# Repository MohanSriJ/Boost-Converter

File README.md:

<div align="center">
  <h1>⚡ DC-DC Boost Converter PCB</h1>
  <h3>🔋 Adjustable Boost Converter Designed in KiCad</h3>
  <p><strong>A custom PCB implementation of an XL6009-based DC-DC boost converter with adjustable output voltage, custom footprints, 3D models, and complete KiCad design files.</strong></p>
</div>

---

## 🎯 Project Overview

This project is a **custom DC-DC Boost Converter PCB** designed using **KiCad**.

The design is based on the **XL6009 boost converter** and includes power filtering, feedback-based output adjustment, custom component footprints, and 3D visualization.

The repository contains the complete design workflow:

`Schematic → PCB Layout → Custom Components → 3D Visualization`

---

## 💡 Project Highlights

### 🔑 Key Capabilities

1. **⚡ XL6009 Boost Converter**

   Implements the XL6009 as the main boost conversion element.

2. **🎚️ Adjustable Output Voltage**

   A potentiometer is used in the feedback network to adjust the converter output.

3. **🔌 Input & Output Filtering**

   Capacitors are used for input and output filtering to support stable converter operation.

4. **🧩 Custom KiCad Components**

   Custom footprints, schematic symbols, and 3D models are included for selected components.

5. **🖥️ Complete PCB Design**

   Includes schematic capture, component placement, routing, copper zones, vias, and PCB visualization.

6. **🧊 3D PCB Visualization**

   KiCad's 3D Viewer is used to verify component placement and visualize the assembled board.

---

## 🧰 Main Components

| Component | Description |
|---|---|
| **XL6009** | DC-DC Boost Converter |
| **DR125-3R3-R** | SMD Power Inductor |
| **SS34** | Schottky Diode |
| **47 µF / 50 V** | Input Capacitor |
| **1 µF** | Input/Output Capacitors |
| **220 µF / 50 V** | Output Capacitor |
| **1 kΩ** | Feedback Resistor |
| **50 kΩ** | Adjustable Potentiometer |
| **Connectors** | Input and Output Connections |

---

## 📐 Schematic Design

The schematic contains the complete boost converter circuit and its supporting components.

### Main Circuit Sections

- 🔌 Input power connection
- 🧲 Power inductor
- ⚡ XL6009 boost converter
- 🔋 Schottky diode
- 🧹 Input filtering
- 🧹 Output filtering
- 🎚️ Feedback voltage adjustment
- 🔌 Output connection

### Schematic

---

## 🖥️ PCB Design

The PCB was designed as a **2-layer board** using KiCad.

The layout focuses on practical component placement, power routing, grounding, and compact organization.

### PCB Design Includes

- 🧩 SMD and through-hole components
- ⚡ Wide power traces
- 🌐 Ground copper zone
- 🔗 Through vias
- 📍 Organized component placement
- 🔌 Input and output terminals
- 🧊 3D component models

### PCB Layout

---

## 🧩 Custom Components

### ⚡ XL6009

A custom KiCad component was created for the XL6009 module.

The folder contains:

- 📐 Custom schematic symbol
- 🧩 Custom PCB footprint
- 🧊 STEP 3D model
- 🖼️ 3D reference image
- 📖 Import instructions

👉 [View XL6009 Resources](./XL6009/)

---

### 🧲 DR125-3R3-R

A custom KiCad component was created for the DR125-3R3-R power inductor.

The folder contains:

- 📐 Schematic symbol
- 🧩 Custom PCB footprint
- 🧊 STEP 3D model
- 🖼️ 3D reference image
- 📖 Import instructions

👉 [View DR125-3R3-R Resources](./DR125-3R3-R/)

---

## 🧊 3D PCB Visualization

The KiCad **3D Viewer** was used to inspect the final PCB design and verify component placement.

### 3D View

### Additional 3D View

---

## 🎥 3D Visualization Video

A 3D visualization video of the PCB is included with the project.

👉 [🎥 View 3D PCB Video](./media/video/)

---

## 📂 Project Documentation

The project is organized into separate sections for easier navigation.

- 📐 [Schematic](./media/schematic/)
- 🖥️ [PCB Layout](./media/pcb-layout/)
- 🧊 [3D View](./media/3d-view/)
- 🎥 [3D Video](./media/video/)
- ⚡ [XL6009 Custom Component](./XL6009/)
- 🧲 [DR125-3R3-R Custom Component](./DR125-3R3-R/)

---

## 🗂️ Repository Structure

```text
DC-DC-Boost-Converter/
│
├── media/
│   ├── schematic/
│   │   └── schematic.png
│   │
│   ├── pcb-layout/
│   │   └── pcb_layout.png
│   │
│   ├── 3d-view/
│   │   ├── 3d_view_1.png
│   │   └── 3d_view_2.png
│   │
│   └── video/
│       └── pcb_3d_view.mp4
│
├── XL6009/
│   ├── README.md
│   ├── XL6009.kicad_sym
│   ├── DPAK170P1435X465-6N.kicad_mod
│   ├── XL6009.step
│   ├── XL6009 3D.png
│   └── how-to-import
│
├── DR125-3R3-R/
│   ├── README.md
│   ├── DR125-3R3-R.kicad_sym
│   ├── INDM1250X1250X600.kicad_mod
│   ├── DR125-3R3-R.step
│   ├── DR125 3D.png
│   └── how-to-import
│
├── Boost Converter.kicad_pcb
├── Boost Converter.kicad_sch
├── Boost Converter.kicad_pro
├── Boost Converter.kicad_prl
└── fp-info-cache
```
## 🛠️ Design Files

The repository contains the complete KiCad project files.

| File Type | Purpose |
|---|---|
| `.kicad_sch` | Schematic design |
| `.kicad_pcb` | PCB layout |
| `.kicad_pro` | KiCad project configuration |
| `.kicad_mod` | Custom PCB footprints |
| `.kicad_sym` | Custom schematic symbols |
| `.step` | 3D component models |

---

## 💻 Software & Tools

### 🖥️ PCB Design

- **KiCad 7.x**

### 📐 Design Tools

- Schematic Capture
- PCB Layout
- Custom Footprint Creation
- Custom Symbol Creation
- STEP 3D Model Integration
- KiCad 3D Viewer

---

## 🔄 Design Workflow

```text
Circuit Concept
      ↓
Schematic Design
      ↓
Component Selection
      ↓
Custom Footprint Creation
      ↓
PCB Component Placement
      ↓
Power & Signal Routing
      ↓
Ground Copper Zone
      ↓
Design Verification
      ↓
3D Model Integration
      ↓
3D PCB Visualization
      ↓
Final PCB Design
```
---

## 📊 PCB Design Overview

| Parameter | Details |
|---|---|
| **Converter Type** | DC-DC Boost Converter |
| **Main Controller** | XL6009 |
| **PCB Layers** | 2 Layer |
| **Design Software** | KiCad 7.x |
| **PCB Type** | Custom Designed PCB |
| **Output** | Adjustable |
| **3D Visualization** | KiCad 3D Viewer |
| **Custom Components** | XL6009, DR125-3R3-R |

---

## ✨ Key Features

- ⚡ XL6009-based boost converter
- 🎚️ Adjustable output voltage
- 🔋 Input and output filtering
- 🧲 Dedicated power inductor
- 🔌 Input and output connectors
- 🧩 Custom KiCad footprints
- 📐 Custom schematic symbols
- 🧊 Custom STEP 3D models
- 🌐 Ground copper zone
- ⚡ Wide power traces
- 🔗 Through vias
- 🖥️ Complete 3D PCB visualization

---

## 📈 Project Status

- ✅ Schematic designed
- ✅ PCB layout completed
- ✅ Component placement completed
- ✅ Power routing completed
- ✅ Ground copper zone added
- ✅ Custom footprints created
- ✅ Custom schematic symbols created
- ✅ 3D models integrated
- ✅ PCB 3D visualization completed
- ✅ Project files organized for GitHub

---

## 🌍 Project Purpose

This project demonstrates the complete process of developing a custom power electronics PCB using KiCad.

It can serve as a reference for learning:

- 🔧 PCB design
- ⚡ Power electronics layout
- 📐 KiCad schematic design
- 🧩 Custom footprint creation
- 🧊 3D model integration
- 🔗 PCB routing
- 📚 Hardware documentation

---

## 👨‍💻 Author

**MohanSriJ**

---

## 📜 License

This project is provided for **educational and design reference purposes**.

Feel free to explore the design files and documentation to understand the PCB development workflow.

---

<div align="center">

⚡ **Designed with KiCad** | 🔋 **Built for Power Electronics** | 🖥️ **Fully Documented**

</div>

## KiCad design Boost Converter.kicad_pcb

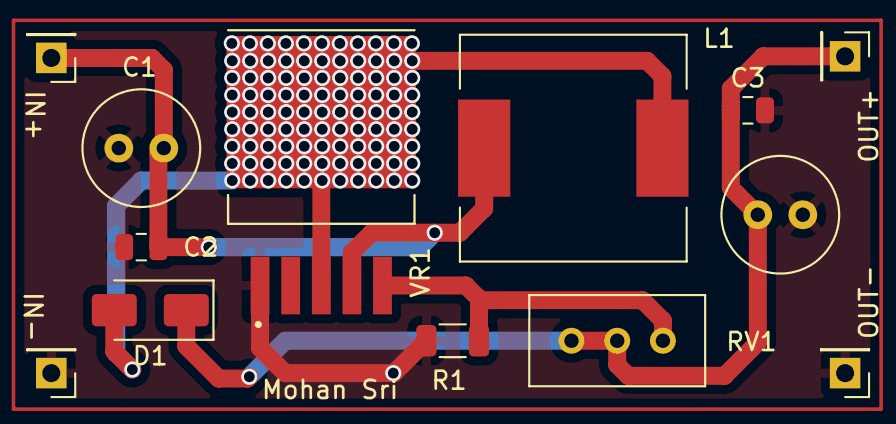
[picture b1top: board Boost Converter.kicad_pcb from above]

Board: 2 copper layers, 13 parts (0 on the bottom side), 5 nets.

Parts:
C1: 47uF/50V; C_Radial_D6.3mm_H11.0mm_P2.50mm
C2, C3: 1uF; C_0805_2012Metric
C4: 220uF/50V; C_Radial_D6.3mm_H11.0mm_P2.50mm
D1: SS34; D_SMA
J1, J2, J3, J4: Conn_01x01_Pin; PinHeader_1x01_P2.54mm_Vertical
L1: 33uH; L_12x12mm_H8mm
R1: 1K; R_1206_3216Metric
RV1: 50K; Potentiometer_Bourns_3296W_Vertical
VR1: XL6009; DPAK170P1435X465-6N

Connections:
GND: C1.2, C2.2, C3.2, C4.2, J2.1, J4.1, R1.2, VR1.1 (GND)
unnamed: D1.2, L1.2, VR1.3 (SW), VR1.6 (SW)
unnamed: C1.1, C2.1, J1.1, L1.1, VR1.4 (VIN)
unnamed: C3.1, C4.1, D1.1, J3.1, RV1.1, RV1.2
unnamed: R1.1, RV1.3, VR1.5 (FB)
